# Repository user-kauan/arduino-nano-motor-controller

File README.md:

# 🔧 Arduino Nano Motor Controller

> Placa de circuito impresso baseada em Arduino Nano para controle PWM de motores DC, com telemetria de corrente, tensão, temperatura e rotação, e proteção térmica automática.

---

## 📌 Sobre o projeto

A placa controla a velocidade de um motor DC via PWM, monitora suas condições de operação em tempo real (corrente, tensão, temperatura e rotação) e interrompe automaticamente o motor em caso de superaquecimento ou sobrecorrente.

## 🖼️ Visão geral

## ⚙️ Funcionalidades

- **Controle de velocidade via PWM**, ajustável remotamente por comando serial
- **Monitoramento de temperatura em tempo real** com sensor DS18B20
- **Telemetria elétrica** via módulo INA219 (corrente, tensão e potência em tempo real por I2C)
- **Medição de RPM** via sensor Hall, usando interrupção externa para não perder pulsos em alta rotação
- **Trava de segurança automática**: desliga o motor em caso de superaquecimento, sobrecorrente, ou falha/desconexão do sensor de temperatura
- **Indicação visual de status** via LEDs (rodando / parado / falha)
- **Log contínuo via Serial** com todos os dados de operação

## 🧰 Especificações e limites da placa

| Especificação | Valor |
|---|---|
| Tensão máxima | 12V DC |
| Corrente máxima do motor | Até 3A em **STALL** (rotor travado) — o motor recomendado para uso contínuo deve consumir **0.5A - 1A** em operação normal, não 3A constantes |
| Fusível recomendado | 5x20mm, **2A**, tipo slow-blow (retardado) |
| Proteções | Soquete para fusível cilíndrico 5x20mm + diodo de proteção 1N5822 |
| Acionamento do motor | MOSFET IRLZ44N |

## 📋 Lista de materiais (BOM)

### Placa principal e circuito

| Qtd | Componente | Descrição |
|---|---|---|
| 1 | Arduino Nano V3 | Microcontrolador principal |
| 1 | MOSFET IRLZ44N | Controle PWM do motor |
| 1 | Diodo 1N5822 | Proteção flyback / roda livre |
| 2 | Borne terminal 5mm (2 pinos) | Entrada de alimentação 12V e saída para o motor |
| 1 | Soquete de fusível | Porta-fusível 5x20mm |
| 2 | LED 5mm | Indicação de status / sinalização |
| 1 | Resistor 4.7kΩ | Pull-up do sensor de temperatura |
| 1 | Resistor 10kΩ | Pull-down do MOSFET |
| 2 | Resistor 220Ω | Limitação de corrente dos LEDs |
| 2 | Header fêmea 1x03 | Sensor Hall e DS18B20 |
| 1 | Header fêmea 1x06 | Conector do módulo INA219 |
| 2 | Header fêmea 1x15 | Soquete para encaixe do Arduino Nano (um de cada lado) |

### Sensores externos suportados

| Sensor | Função | Comunicação |
|---|---|---|
| DS18B20 | Temperatura | 1-Wire
| INA219 | Corrente, tensão e potência | I2C |
| Sensor Hall (3 pinos) | Rotação / RPM | Digital |

## 🔌 Montagem

O Arduino Nano é encaixado diretamente nos headers da própria PCB — não há fiação manual entre o microcontrolador e os componentes da placa, já que o layout do circuito fixa essas conexões fisicamente. Basta encaixar o Nano na posição correta (a serigrafia indica a orientação) e conectar os sensores externos (DS18B20, INA219, sensor Hall) nos headers dedicados.

> 💡 **Sobre a soldagem:** é possível soldar todos os componentes diretamente na placa, incluindo o próprio Arduino Nano direto nos pinos da PCB, sem usar headers. **A recomendação, porém, é usar headers fêmea** (os 1x15 para o Nano e os menores para os sensores). Isso permite remover o Arduino ou os sensores para testes, reprogramação fora da placa, ou substituição em caso de defeito, sem precisar dessoldar nada.

**Mapeamento fixo definido pela placa:**

| Função | Pino do Nano |
|---|---|
| PWM do motor (gate do MOSFET) | D9 |
| DS18B20 (temperatura) | D3 |
| Sensor Hall (RPM) | D2 |
| INA219 (I2C) | A4 (SDA) / A5 (SCL) |
| LED — motor rodando | D11 |
| LED — motor parado / falha | D10 |

## 🖥️ Firmware

O código-fonte está em [`motor_code.ino`](./motor_code.ino).

### Bibliotecas necessárias
Instale pelo Gerenciador de Bibliotecas da Arduino IDE:
- `OneWire`
- `DallasTemperature`
- `Adafruit INA219` (+ `Adafruit BusIO`)

### Comandos via Serial (9600 baud)

| Comando | Ação |
|---|---|
| `Vxxx` | Define a velocidade do motor (0–255). Ex: `V150` |
| `S` | Para o motor |
| `R` | Reseta uma falha de segurança (temperatura, corrente ou sensor desconectado) |

### Lógica de segurança
- Se a temperatura ultrapassar **70°C**, o motor é desligado automaticamente
- Se a corrente ultrapassar **3A**, o motor é desligado automaticamente
- Se o sensor DS18B20 desconectar ou falhar, o motor também é desligado (falha "às cegas" não é permitida)
- Uma vez em falha, o motor **permanece desligado** até o comando `R` ser enviado — evita religamento automático indesejado

### Como gravar
1. Abra `motor_code.ino` na Arduino IDE
2. Selecione a placa **Arduino Nano** e a porta serial correta
3. Instale as bibliotecas listadas acima
4. Grave e abra o Monitor Serial (9600 baud) para acompanhar os dados em tempo real

## 🖥️ Hardware — como fabricar

1. Baixe os arquivos de fabricação em [`Gerbers_Files.zip`](./Gerbers_Files.zip) e mande fabricar a placa (usado PCBWay no projeto original)
2. Solde os componentes conforme a lista de materiais acima
3. Conecte os sensores externos nos headers correspondentes
4. Conecte a alimentação de 12V e o motor DC nos bornes terminais

### Abrindo o projeto no KiCad
```
PCB_Motor.kicad_pro   → projeto principal (abra este primeiro)
PCB_Motor.kicad_sch   → esquemático
PCB_Motor.kicad_pcb   → layout da placa
```

## 📂 Estrutura do repositório

```
├── 3D_View_PCB.png            → render 3D da placa
├── SCH.png                     → imagem do esquemático
├── Gerbers_Files.zip           → arquivos para fabricação
├── PCB_Motor.kicad_pcb         → layout da placa (KiCad)
├── PCB_Motor.kicad_pro         → projeto KiCad
├── PCB_Motor.kicad_sch         → esquemático (KiCad)
├── motor_code.ino              → código-fonte do Arduino
├── LICENSE                     → MIT
└── README.md
```

## 📄 Licença

Este projeto está sob a licença MIT — veja o arquivo [LICENSE](./LICENSE) para mais detalhes.

---

#Engenharia #Eletronica #Hardware #PCBDesign #KiCad #Arduino #FirjanSENAI #SistemasEmbarcados #GitHub #OpenSource #Automação

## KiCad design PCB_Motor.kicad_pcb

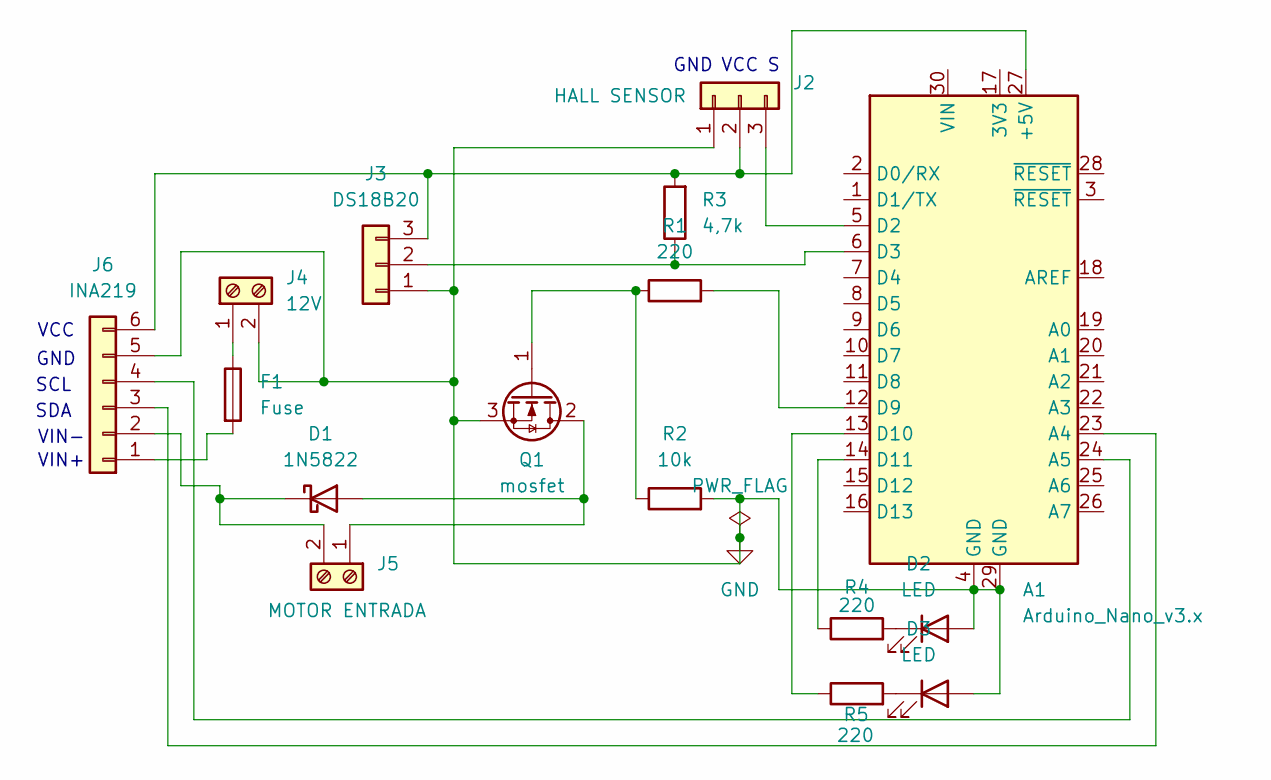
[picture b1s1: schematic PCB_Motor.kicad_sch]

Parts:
A1: Arduino_Nano_v3.x; Arduino_Nano
D1: 1N5822; D_DO-201AD_P15.24mm_Horizontal
D2, D3: LED; LED_D5.0mm
F1: Fuse; Fuseholder_Cylinder-5x20mm_Schurter_0031_8201_Horizontal_Op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
J2: HALL SENSOR; PinSocket_1x03_P2.54mm_Vertical
J3: DS18B20; PinSocket_1x03_P2.54mm_Vertical
J4: 12V; TerminalBlock_MaiXu_MX126-5.0-02P_1x02_P5.00mm
J5: MOTOR ENTRADA; TerminalBlock_MaiXu_MX126-5.0-02P_1x02_P5.00mm
J6: INA219; PinSocket_1x06_P2.54mm_Vertical
Q1: mosfet; TO-220-3_Vertical
R1, R4, R5: 220; R_Axial_DIN0207_L6.3mm_D2.5mm_P10.16mm_Horizontal
R2: 10k; R_Axial_DIN0207_L6.3mm_D2.5mm_P10.16mm_Horizontal
R3: 4,7k; R_Axial_DIN0207_L6.3mm_D2.5mm_P10.16mm_Horizontal

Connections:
GND: A1.4 (GND), A1.29 (GND), D2.2 (A), D3.2 (A), J2.1, J3.1, J4.2, J6.5, Q1.3 (S), R2.2
unnamed: A1.27 (+5V), J2.2, J3.3, J6.6, R3.2
unnamed: A1.23 (A4), J6.3
unnamed: A1.24 (A5), J6.4
unnamed: A1.5 (D2), J2.3
unnamed: A1.6 (D3), J3.2, R3.1
unnamed: A1.12 (D9), R1.2
unnamed: A1.13 (D10), R5.1
unnamed: A1.14 (D11), R4.1
unnamed: D1.2 (A), J5.1, Q1.2 (D)
unnamed: D1.1 (K), J5.2, J6.2
unnamed: D2.1 (K), R4.2
unnamed: D3.1 (K), R5.2
unnamed: F1.1, J4.1
unnamed: F1.2, J6.1
unnamed: Q1.1 (G), R1.1, R2.1

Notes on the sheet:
GND
GND
VIN+
SDA
SCL
VCC
VCC
VIN-

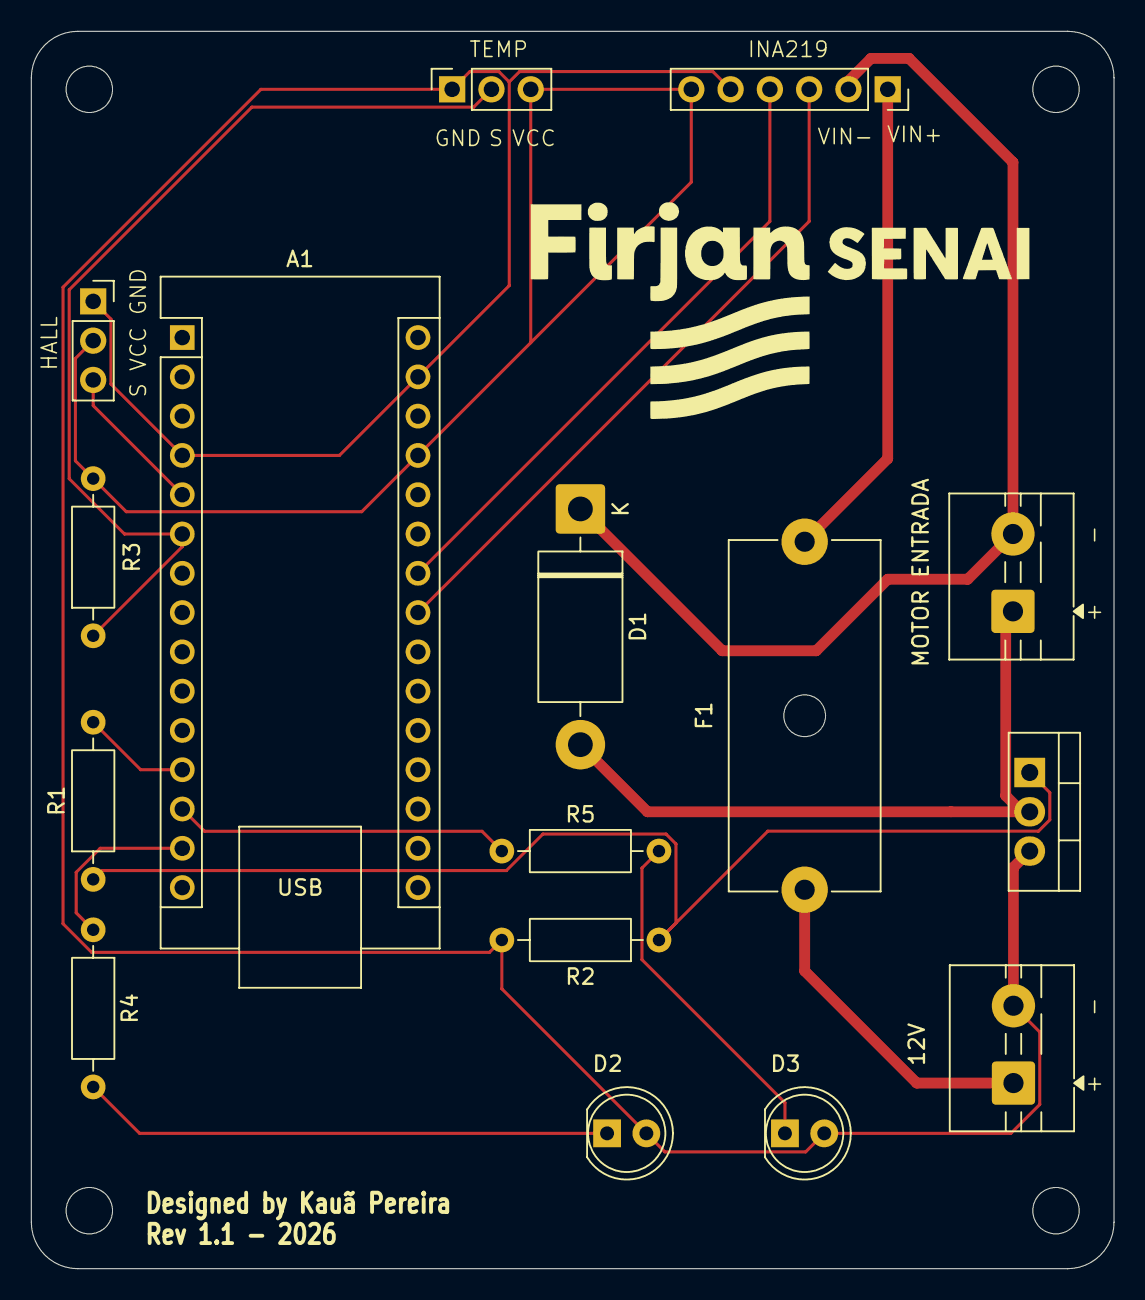
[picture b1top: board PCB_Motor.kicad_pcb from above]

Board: 2 copper layers, 70.0 x 80.0 mm, 16 parts (0 on the bottom side), 16 nets.
